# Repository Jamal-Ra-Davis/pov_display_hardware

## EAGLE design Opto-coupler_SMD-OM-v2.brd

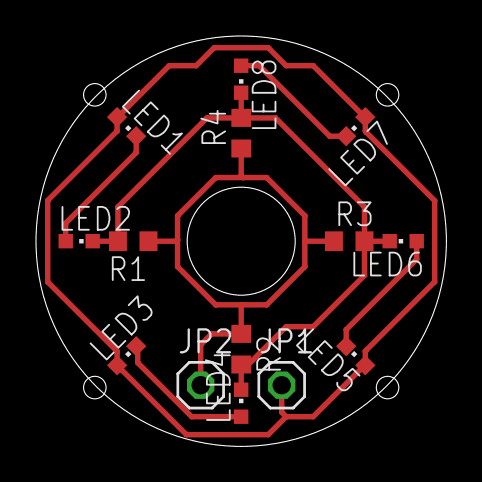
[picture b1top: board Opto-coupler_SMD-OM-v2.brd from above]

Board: 2 copper layers, 22.8 x 22.8 mm, 14 parts (0 on the bottom side), 7 nets.

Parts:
JP1, JP2: 1X01
LED1, LED2, LED3, LED4, LED5, LED6, LED7, LED8: CHIPLED_0603
R1, R2, R3, R4: 100; R0603

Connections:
GND: JP2.1, R1.1, R2.1, R3.1, R4.1
unnamed: LED1.C, LED2.A
unnamed: LED2.C, LED4.C, LED6.C, LED8.C, R1.2, R2.2, R3.2, R4.2
unnamed: LED3.C, LED4.A
unnamed: LED5.C, LED6.A
unnamed: LED7.C, LED8.A
VCC: JP1.1, LED1.A, LED3.A, LED5.A, LED7.A

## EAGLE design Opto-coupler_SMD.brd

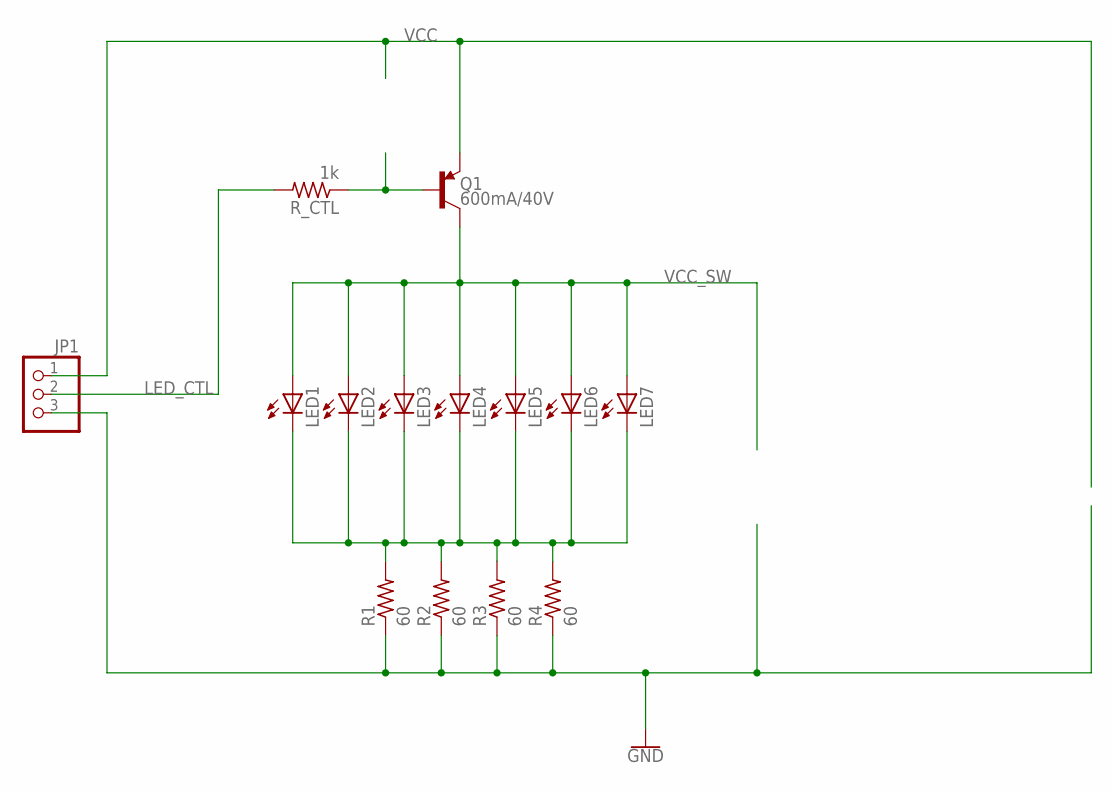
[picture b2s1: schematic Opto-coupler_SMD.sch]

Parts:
JP1: PINHD-1X3; 1X03
LED1, LED2, LED3, LED4, LED5, LED6, LED7: LEDCHIPLED_0603; CHIPLED_0603
Q1: 600mA/40V; SOT23-3
R1, R2, R3, R4: 60; R0603
R_CTL: 1k; R0603

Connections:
GND: JP1.3, R1.1, R2.1, R3.1, R4.1
LED_CTL: JP1.2, R_CTL.2
unnamed: Q1.1 (B), R_CTL.1
unnamed: LED1.C, LED2.C, LED3.C, LED4.C, LED5.C, LED6.C, LED7.C, R1.2, R2.2, R3.2, R4.2
VCC: JP1.1, Q1.2 (E)
VCC_SW: LED1.A, LED2.A, LED3.A, LED4.A, LED5.A, LED6.A, LED7.A, Q1.3 (C)

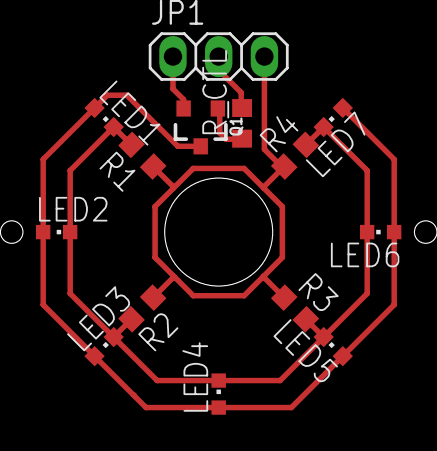
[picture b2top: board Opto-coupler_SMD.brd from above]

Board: 2 copper layers, 14 parts (0 on the bottom side), 6 nets.

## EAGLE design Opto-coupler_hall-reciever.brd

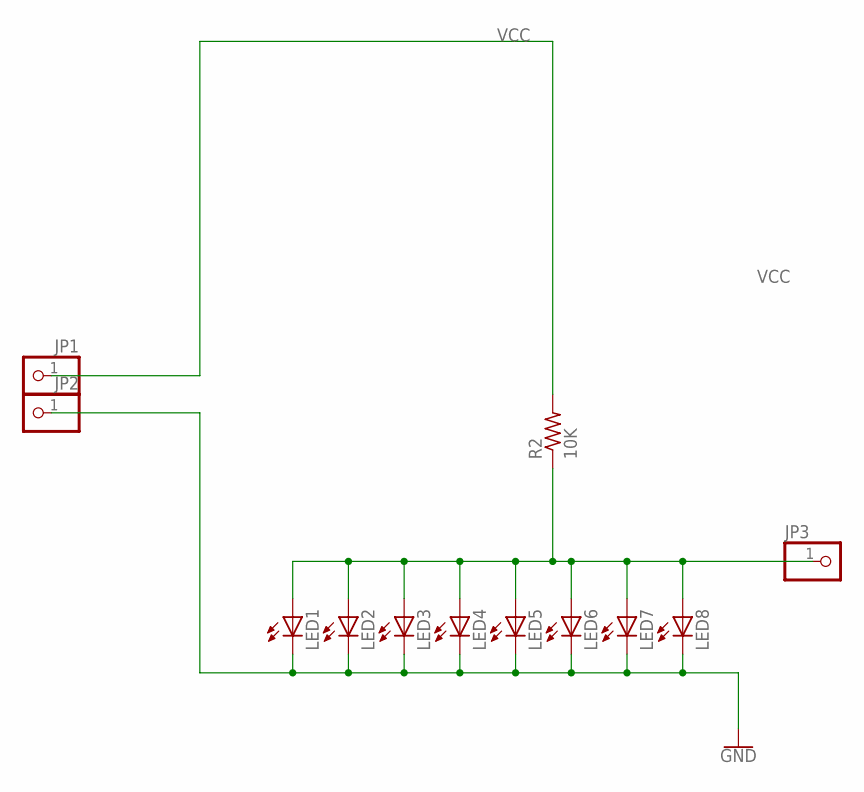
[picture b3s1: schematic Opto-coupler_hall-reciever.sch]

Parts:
JP1, JP2, JP3: PINHD-1X1; 1X01
LED1, LED2, LED3, LED4, LED5, LED6, LED7, LED8: LEDCHIP-LED0603; CHIP-LED0603
R2: 10K; R0603

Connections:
GND: JP2.1, LED1.C, LED2.C, LED3.C, LED4.C, LED5.C, LED6.C, LED7.C, LED8.C
unnamed: JP3.1, LED1.A, LED2.A, LED3.A, LED4.A, LED5.A, LED6.A, LED7.A, LED8.A, R2.1
VCC: JP1.1, R2.2

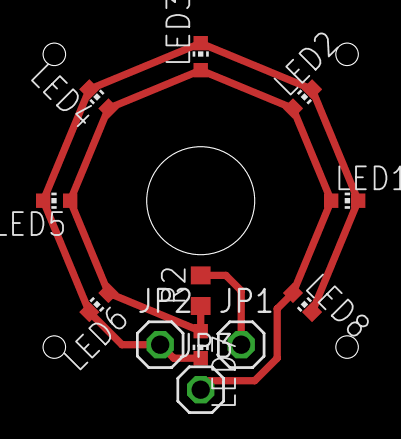
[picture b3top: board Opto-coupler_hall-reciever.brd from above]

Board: 2 copper layers, 12 parts (0 on the bottom side), 3 nets.

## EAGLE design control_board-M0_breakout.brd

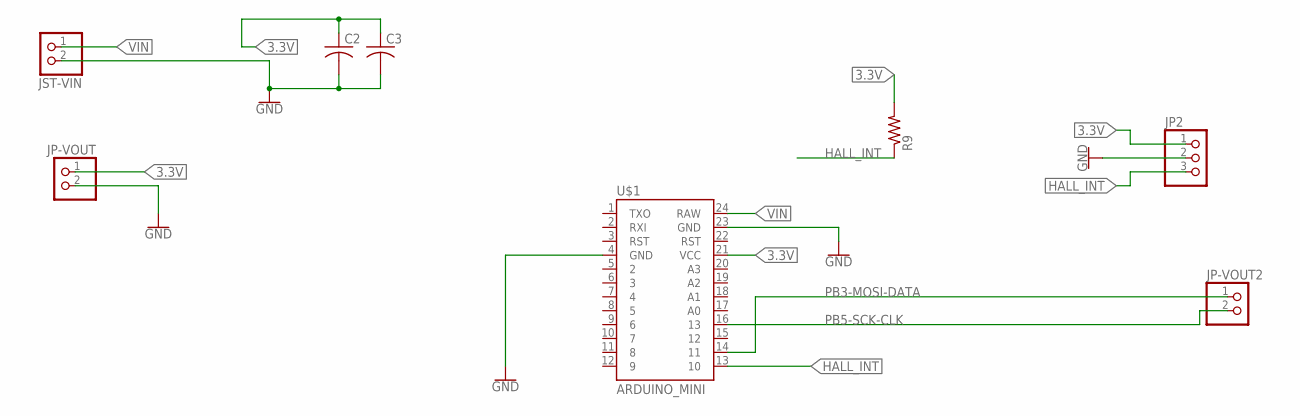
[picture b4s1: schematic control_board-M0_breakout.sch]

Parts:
C2, C3: C-US025-060X050; C025-060X050
JP2: PINHD-1X3; 1X03
JP-VOUT, JP-VOUT2: PINHD-1X2; 1X02
JST-VIN: JST_2PIN-THM-RA; JST-PH-2-THM-RA
R9: R-US_0207/7; 0207/7
U$1: ARDUINO_MINI

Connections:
3.3V: C2.1, C3.1, JP2.1, JP-VOUT.1, R9.2, U$1.21 (VCC)
GND: C2.2, C3.2, JP2.2, JP-VOUT.2, JST-VIN.2 (1), U$1.4 (GND), U$1.23 (GND)
HALL_INT: JP2.3, R9.1, U$1.13 (10)
PB3-MOSI-DATA: JP-VOUT2.1, U$1.14 (11)
PB5-SCK-CLK: JP-VOUT2.2, U$1.16 (13)
VIN: JST-VIN.1 (2), U$1.24 (RAW)

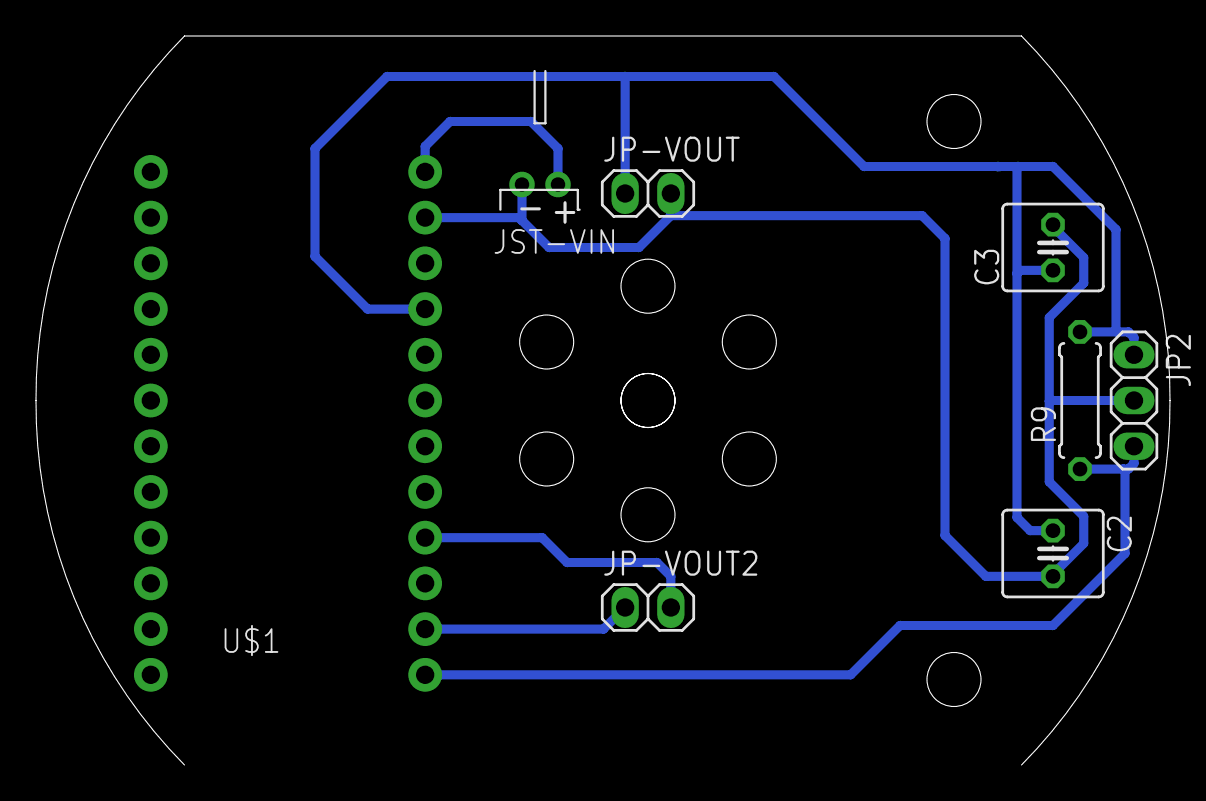
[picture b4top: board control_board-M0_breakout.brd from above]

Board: 2 copper layers, 63.0 x 40.5 mm, 8 parts (0 on the bottom side), 6 nets.

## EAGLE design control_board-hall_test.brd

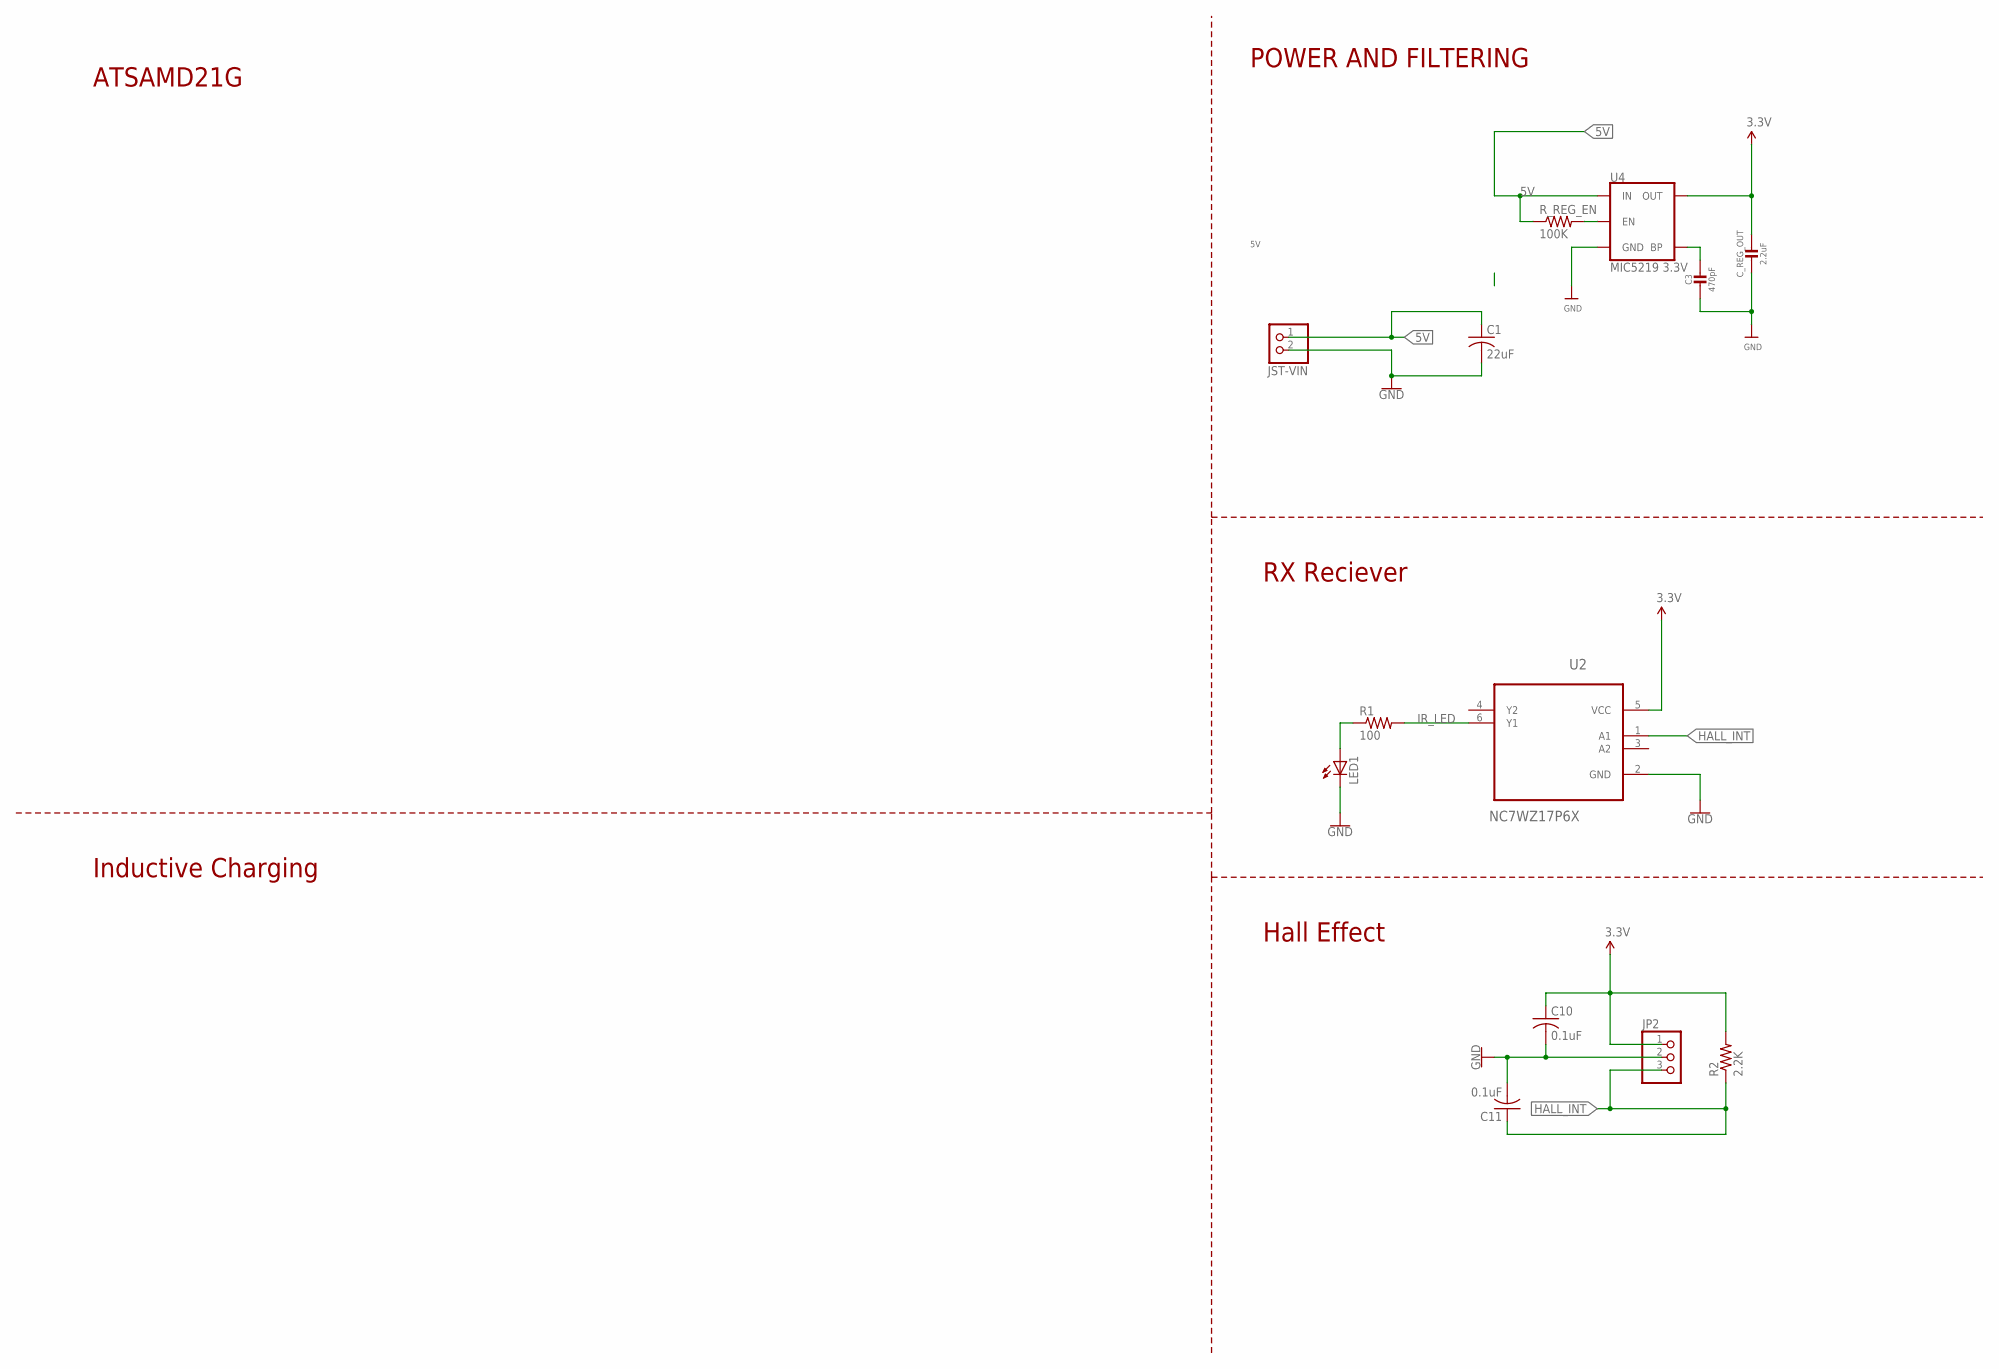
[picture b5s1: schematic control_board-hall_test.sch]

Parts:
C1: 22uF; C1206
C3: 470pF; 0603-NO
C10, C11: 0.1uF; C0603
C_REG_OUT: 2.2uF; 0805-NO
JP2: PINHD-1X3; 1X03
JST-VIN: JST_2PIN-THM-RA; JST-PH-2-THM-RA
LED1: LED3MM
R1: 100; 0207/9
R2: 2.2K; 0207/9
R_REG_EN: 100K; R0603
U2: NC7WZ17P6X; SOT65P210X110-6N
U4: MIC5219 3.3V; SOT23-5

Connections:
3.3V: C10.1, C_REG_OUT.1, JP2.1, R2.2, U2.5 (VCC), U4.5 (OUT)
5V: C1.1, JST-VIN.1 (2), R_REG_EN.1, U4.1 (IN)
GND: C1.2, C3.2, C10.2, C11.2, C_REG_OUT.2, JP2.2, JST-VIN.2 (1), LED1.K (C), U2.2 (GND), U4.2 (GND)
HALL_INT: C11.1, JP2.3, R2.1, U2.1 (A1)
IR_LED: R1.2, U2.6 (Y1)
unnamed: LED1.A, R1.1
unnamed: R_REG_EN.2, U4.3 (EN)
unnamed: C3.1, U4.4 (BP)

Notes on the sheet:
POWER AND FILTERING
ATSAMD21G
Inductive Charging
RX Reciever
Hall Effect

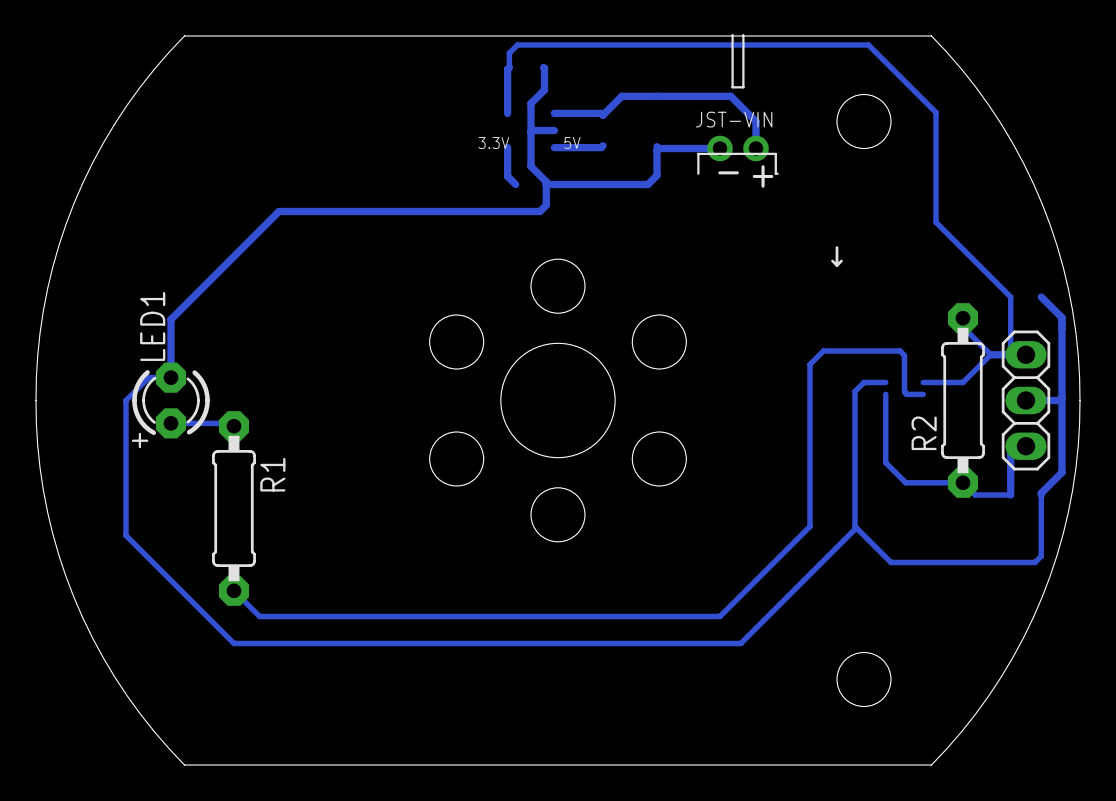
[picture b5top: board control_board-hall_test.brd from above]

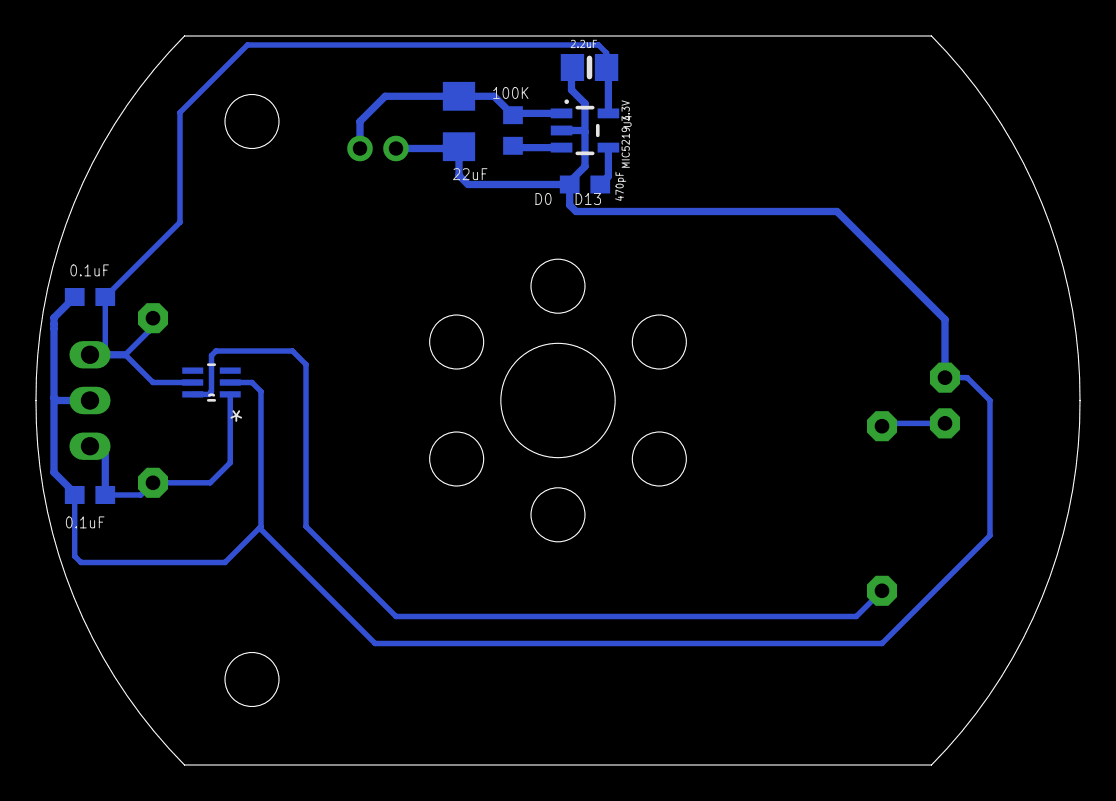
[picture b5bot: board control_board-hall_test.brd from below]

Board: 2 copper layers, 58.0 x 40.5 mm, 13 parts (8 on the bottom side), 8 nets.

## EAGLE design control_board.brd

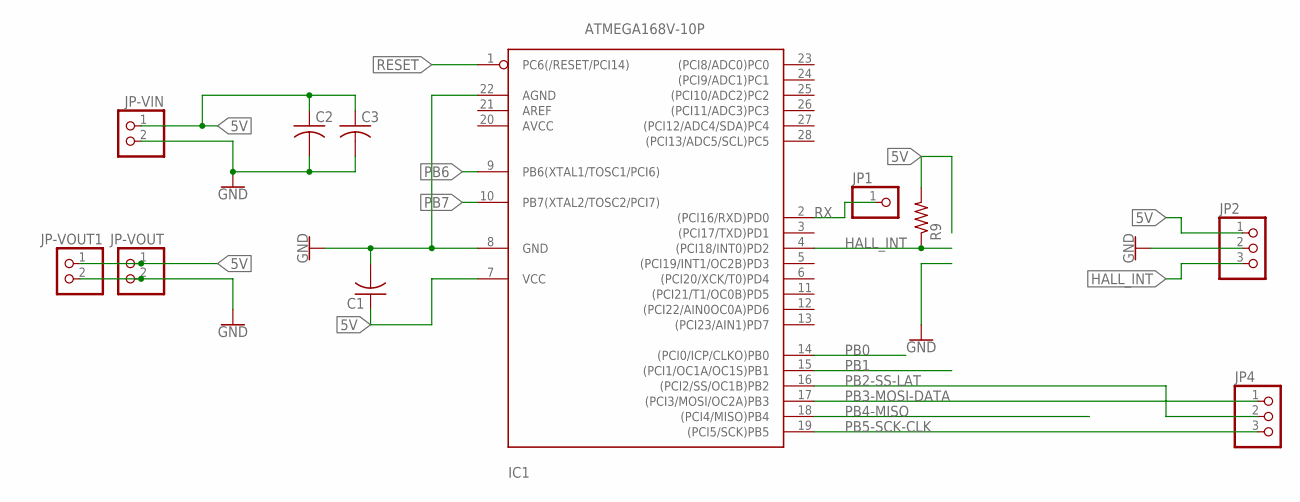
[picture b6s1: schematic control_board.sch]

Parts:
C1: C-US025-030X050; C025-030X050
C2, C3: C-US025-060X050; C025-060X050
IC1: ATMEGA168V-10P; DIL28-3
JP1: PINHD-1X1; 1X01
JP2, JP4: PINHD-1X3; 1X03
JP-VIN: PINHD-1X2; 1X02
JP-VOUT, JP-VOUT1: PINHD-1X2; 1X02
R9: R-US_0207/7; 0207/7

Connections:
5V: C1.1, C2.1, C3.1, IC1.7 (VCC), JP2.1, JP-VIN.1, JP-VOUT.1, JP-VOUT1.1, R9.2
GND: C1.2, C2.2, C3.2, IC1.8 (GND), IC1.22 (AGND), JP2.2, JP-VIN.2, JP-VOUT.2, JP-VOUT1.2
HALL_INT: IC1.4 ((PCI18/INT0)PD2), JP2.3, R9.1
PB0: IC1.14 ((PCI0/ICP/CLKO)PB0)
PB1: IC1.15 ((PCI1/OC1A/OC1S)PB1)
PB2-SS-LAT: IC1.16 ((PCI2/SS/OC1B)PB2), JP4.2
PB3-MOSI-DATA: IC1.17 ((PCI3/MOSI/OC2A)PB3), JP4.1
PB4-MISO: IC1.18 ((PCI4/MISO)PB4)
PB5-SCK-CLK: IC1.19 ((PCI5/SCK)PB5), JP4.3
PB6: IC1.9 (PB6(XTAL1/TOSC1/PCI6))
PB7: IC1.10 (PB7(XTAL2/TOSC2/PCI7))
RESET: IC1.1 (PC6(/RESET/PCI14))
RX: IC1.2 ((PCI16/RXD)PD0), JP1.1

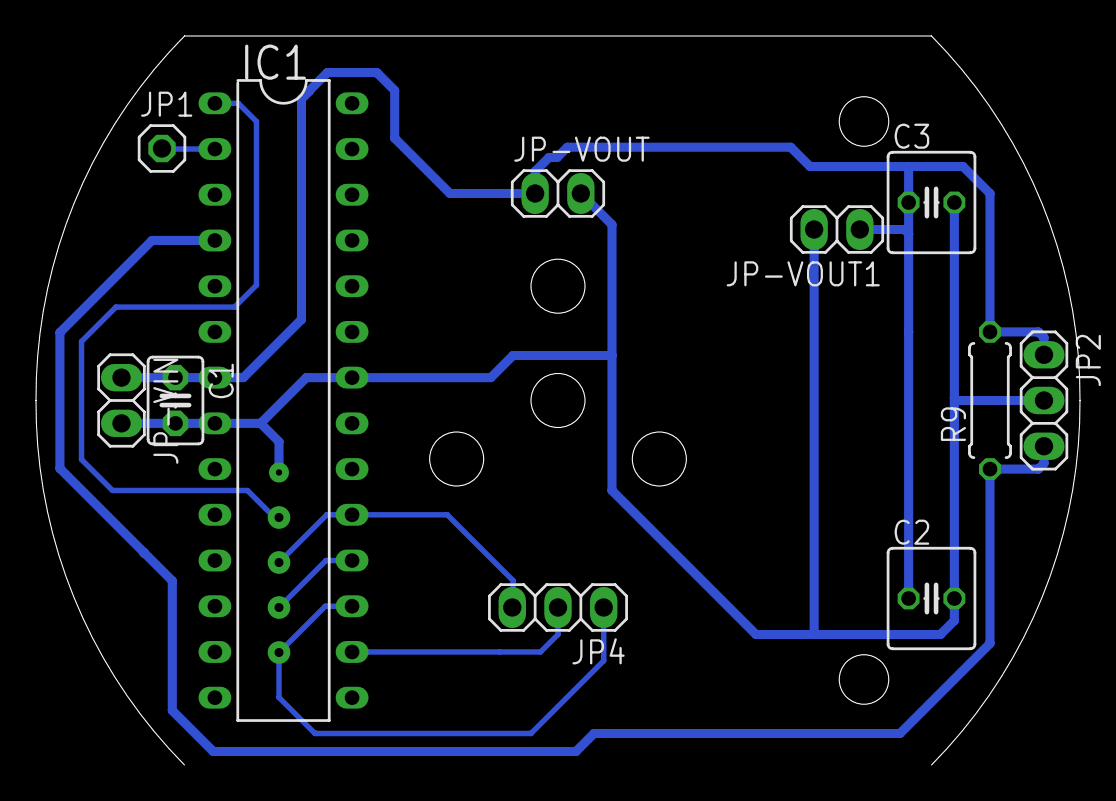
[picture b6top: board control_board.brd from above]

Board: 2 copper layers, 58.0 x 40.5 mm, 11 parts (0 on the bottom side), 7 nets.

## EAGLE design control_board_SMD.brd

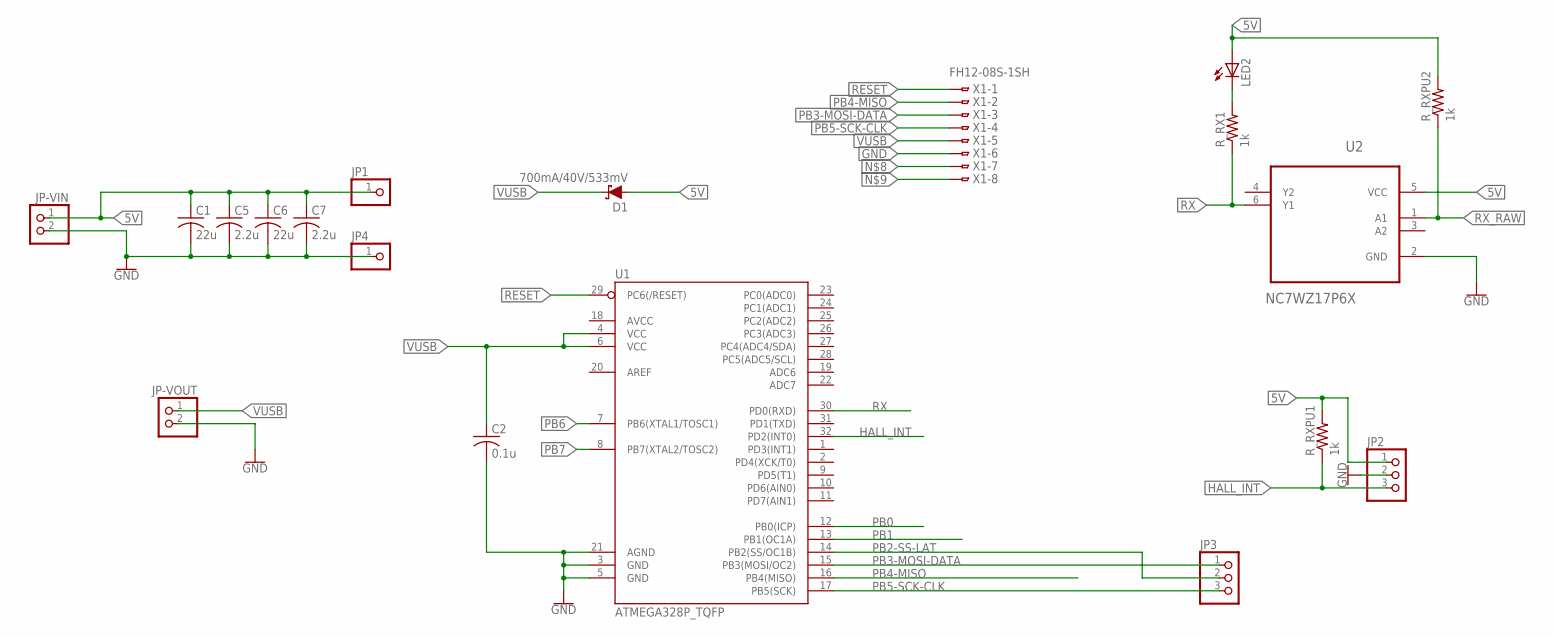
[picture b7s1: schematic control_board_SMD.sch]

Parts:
C1, C6: 22u; C1210
C2: 0.1u; C0603
C5, C7: 2.2u; C1210
D1: 700mA/40V/533mV; SOT23-3
JP1, JP4: PINHD-1X1; 1X01
JP2, JP3: PINHD-1X3; 1X03
JP-VIN: PINHD-1X2; 1X02
JP-VOUT: PINHD-1X2; 1X02
LED2: LEDCHIPLED_0603; CHIPLED_0603
R_RX1: 1k; R0603
R_RXPU1, R_RXPU2: 1k; R0603
U1: ATMEGA328P_TQFP; TQFP32-08
U2: NC7WZ17P6X; SOT65P210X110-6N
X1: FH12-08S-1SH

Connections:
5V: C1.1, C5.1, C6.1, C7.1, D1.1 (A), JP1.1, JP2.1, JP-VIN.1, LED2.A, R_RXPU1.2, R_RXPU2.2, U2.5 (VCC)
GND: C1.2, C2.2, C5.2, C6.2, C7.2, JP2.2, JP4.1, JP-VIN.2, JP-VOUT.2, U1.3 (GND), U1.5 (GND), U1.21 (AGND), U2.2 (GND), X1.6
HALL_INT: JP2.3, R_RXPU1.1, U1.32 (PD2(INT0))
unnamed: LED2.C, R_RX1.2
PB0: U1.12 (PB0(ICP))
PB1: U1.13 (PB1(OC1A))
PB2-SS-LAT: JP3.2, U1.14 (PB2(SS/OC1B))
PB3-MOSI-DATA: JP3.1, U1.15 (PB3(MOSI/OC2)), X1.3
PB4-MISO: U1.16 (PB4(MISO)), X1.2
PB5-SCK-CLK: JP3.3, U1.17 (PB5(SCK)), X1.4
PB6: U1.7 (PB6(XTAL1/TOSC1))
PB7: U1.8 (PB7(XTAL2/TOSC2))
RESET: U1.29 (PC6(/RESET)), X1.1
RX: R_RX1.1, U1.30 (PD0(RXD)), U2.6 (Y1)
RX_RAW: R_RXPU2.1, U2.1 (A1)
VUSB: C2.1, D1.3 (C), JP-VOUT.1, U1.4 (VCC), U1.6 (VCC), X1.5

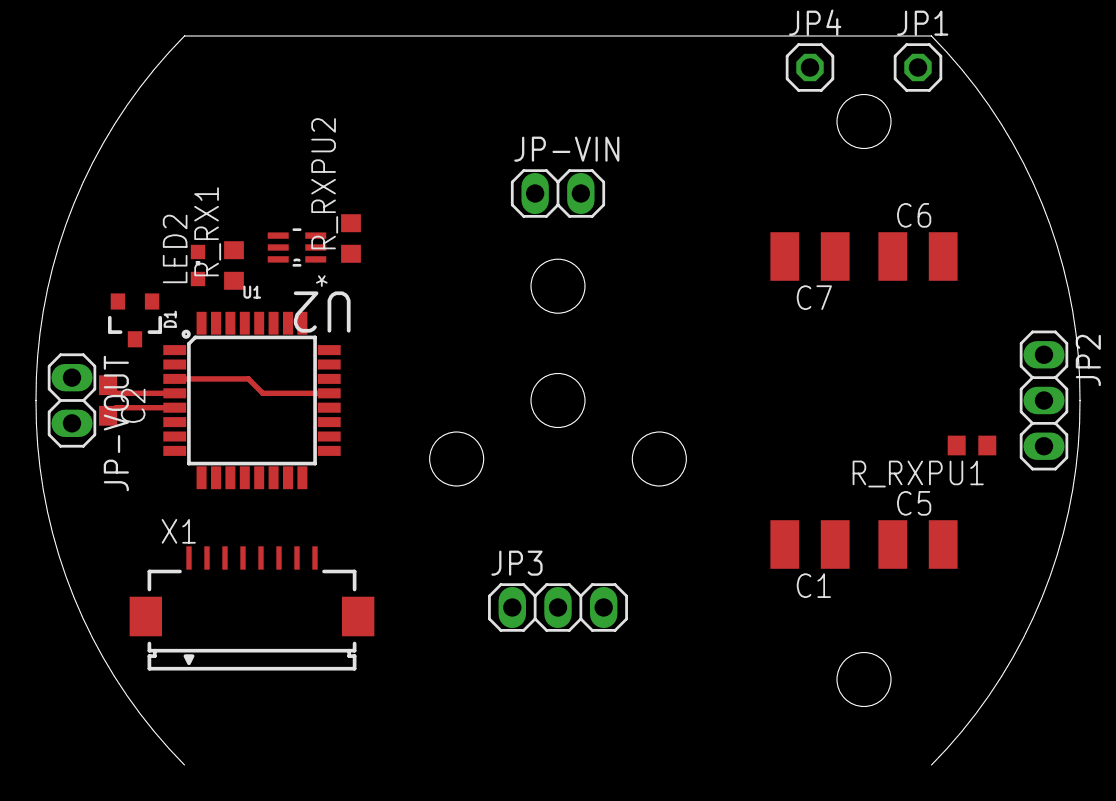
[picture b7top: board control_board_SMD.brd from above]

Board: 2 copper layers, 58.0 x 40.5 mm, 19 parts (0 on the bottom side), 12 nets.

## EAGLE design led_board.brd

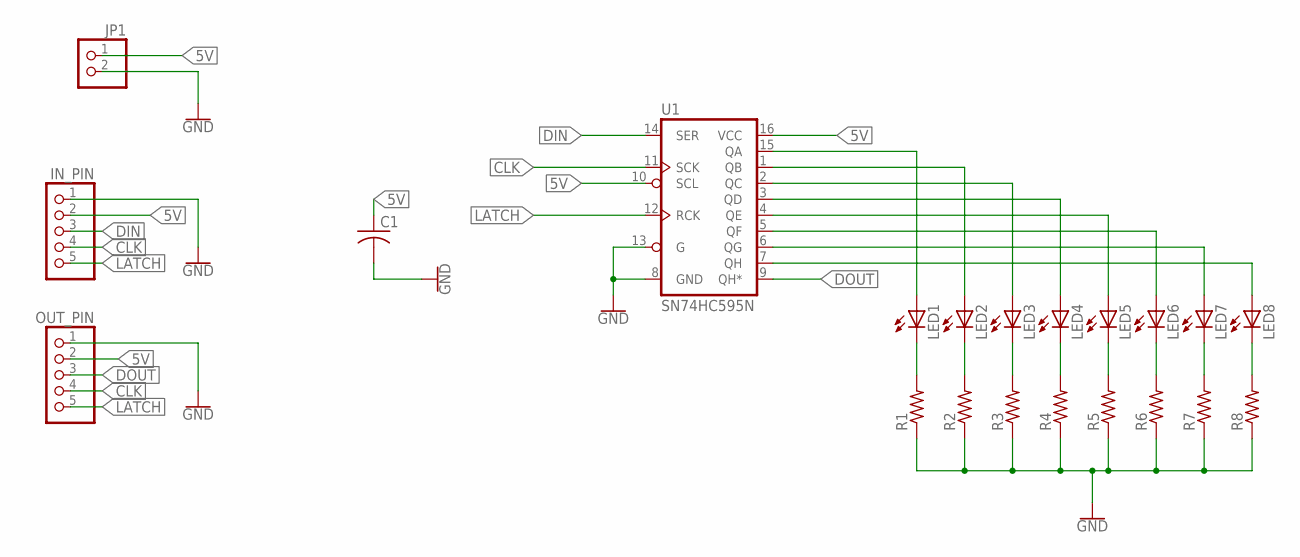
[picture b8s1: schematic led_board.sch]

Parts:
C1: C-US025-030X050; C025-030X050
IN_PIN: PINHD-1X5; 1X05
JP1: PINHD-1X2; 1X02
LED1, LED2, LED3, LED4, LED5, LED6, LED7, LED8: LED3MM
OUT_PIN: PINHD-1X5; 1X05
R1, R2, R3, R4, R5, R6, R7, R8: R-US_0207/7; 0207/7
U1: SN74HC595N; DIP16

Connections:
5V: C1.1, IN_PIN.2, JP1.1, OUT_PIN.2, U1.10 (SCL), U1.16 (VCC)
CLK: IN_PIN.4, OUT_PIN.4, U1.11 (SCK)
DIN: IN_PIN.3, U1.14 (SER)
DOUT: OUT_PIN.3, U1.9 (QH*)
GND: C1.2, IN_PIN.1, JP1.2, OUT_PIN.1, R1.1, R2.1, R3.1, R4.1, R5.1, R6.1, R7.1, R8.1, U1.8 (GND), U1.13 (G)
LATCH: IN_PIN.5, OUT_PIN.5, U1.12 (RCK)
unnamed: LED1.K (C), R1.2
unnamed: LED2.K (C), R2.2
unnamed: LED3.K (C), R3.2
unnamed: LED4.K (C), R4.2
unnamed: LED5.K (C), R5.2
unnamed: LED6.K (C), R6.2
unnamed: LED7.K (C), R7.2
unnamed: LED8.K (C), R8.2
unnamed: LED1.A, U1.15 (QA)
unnamed: LED2.A, U1.1 (QB)
unnamed: LED3.A, U1.2 (QC)
unnamed: LED4.A, U1.3 (QD)
unnamed: LED5.A, U1.4 (QE)
unnamed: LED6.A, U1.5 (QF)
unnamed: LED7.A, U1.6 (QG)
unnamed: LED8.A, U1.7 (QH)

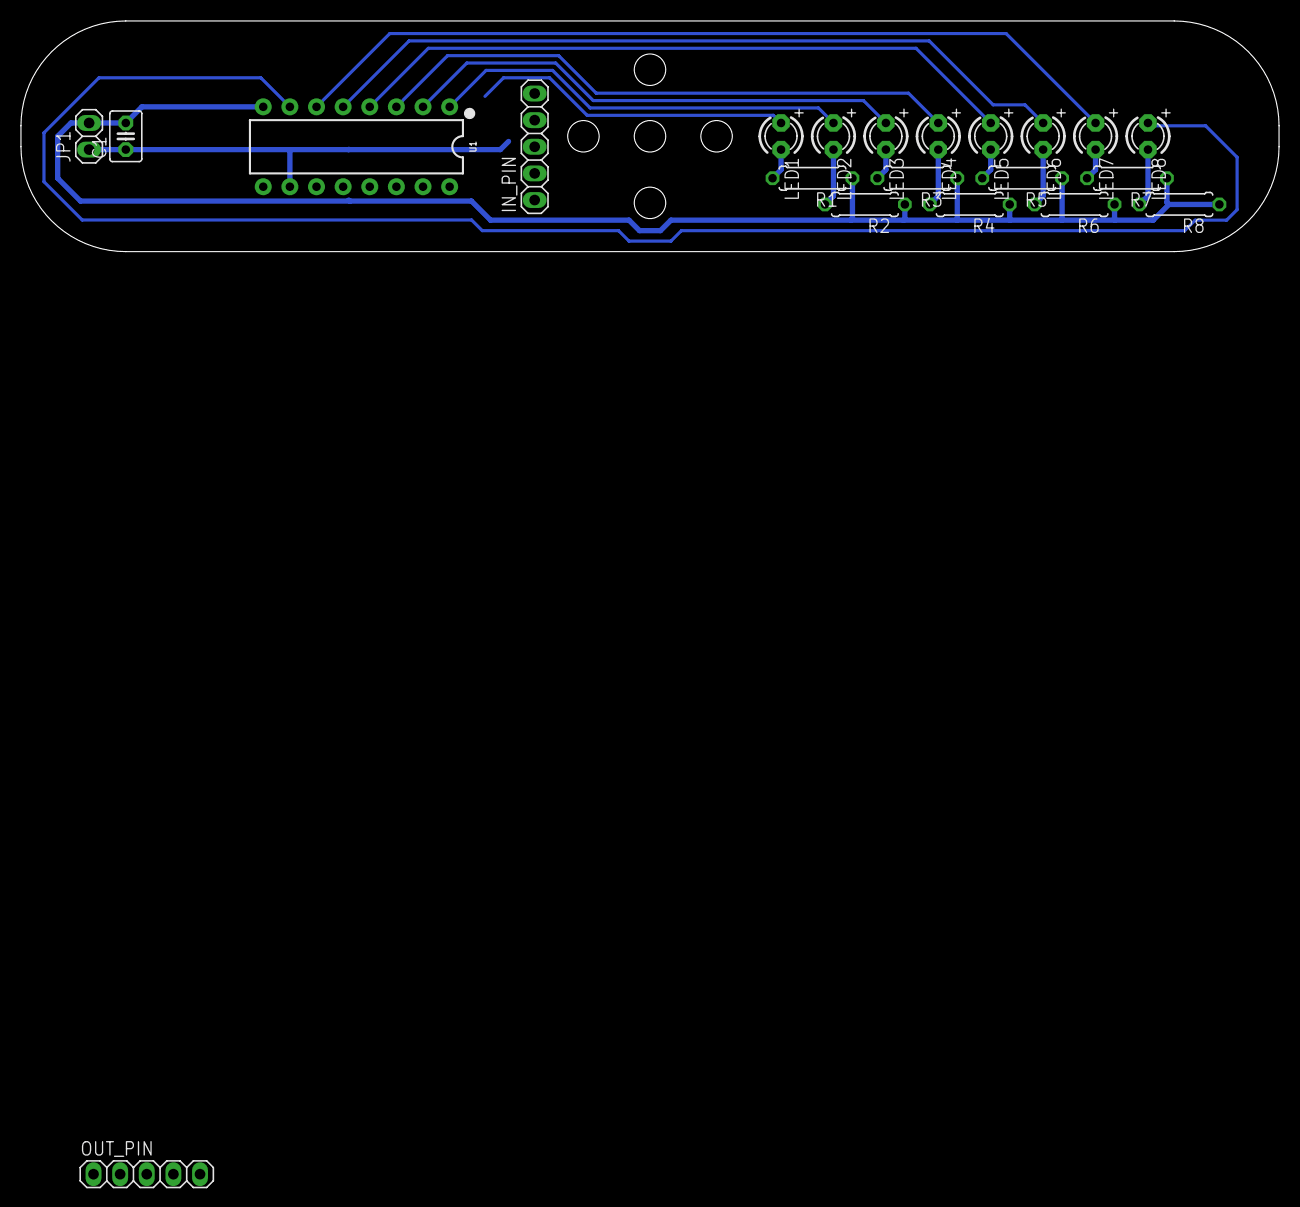
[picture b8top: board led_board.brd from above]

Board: 2 copper layers, 120.0 x 22.0 mm, 21 parts (0 on the bottom side), 22 nets.

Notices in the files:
parts and their libraries:
SparkFun-DiscreteSemi: Licensing: Creative Commons ShareAlike 4.0 International - https://creativecommons.org/licenses/by-sa/4.0
microbuilder: This work is placed in the public domain, and may be freely used for commercial and non-commercial work with the following conditions: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
